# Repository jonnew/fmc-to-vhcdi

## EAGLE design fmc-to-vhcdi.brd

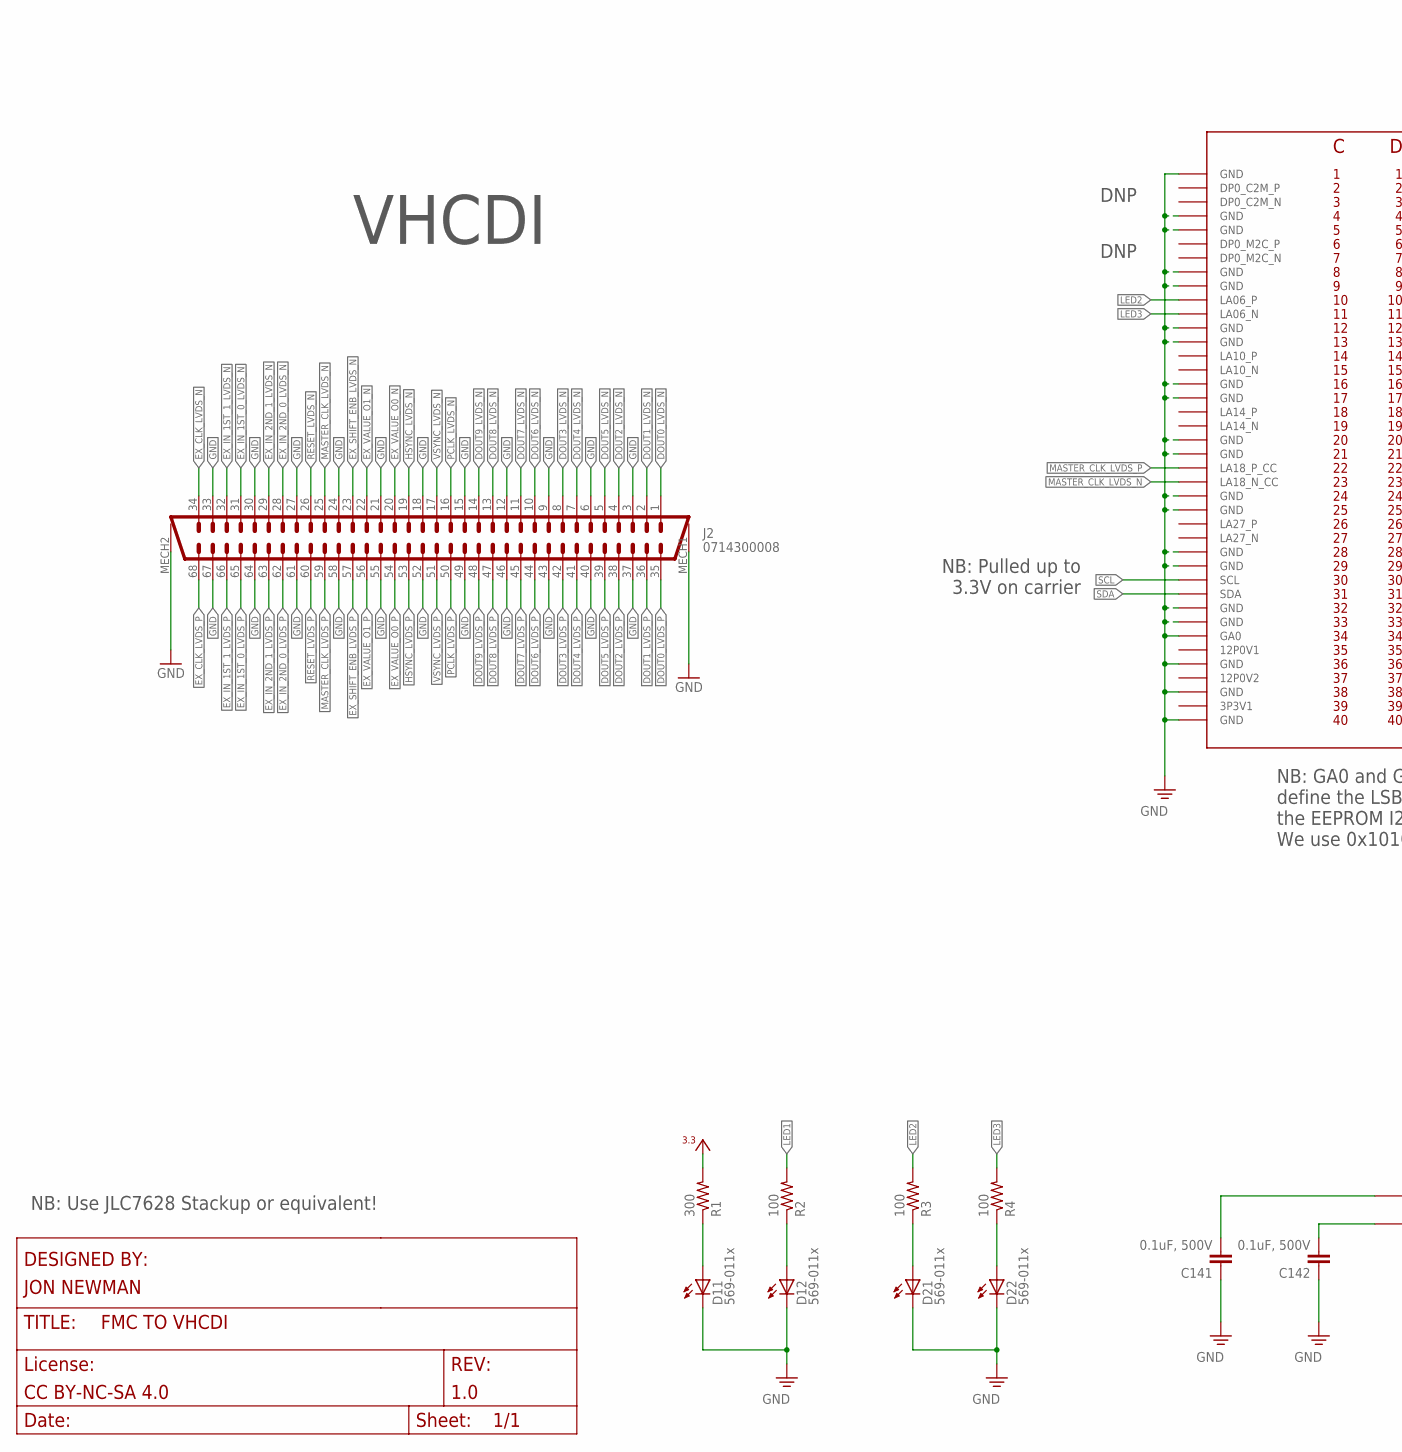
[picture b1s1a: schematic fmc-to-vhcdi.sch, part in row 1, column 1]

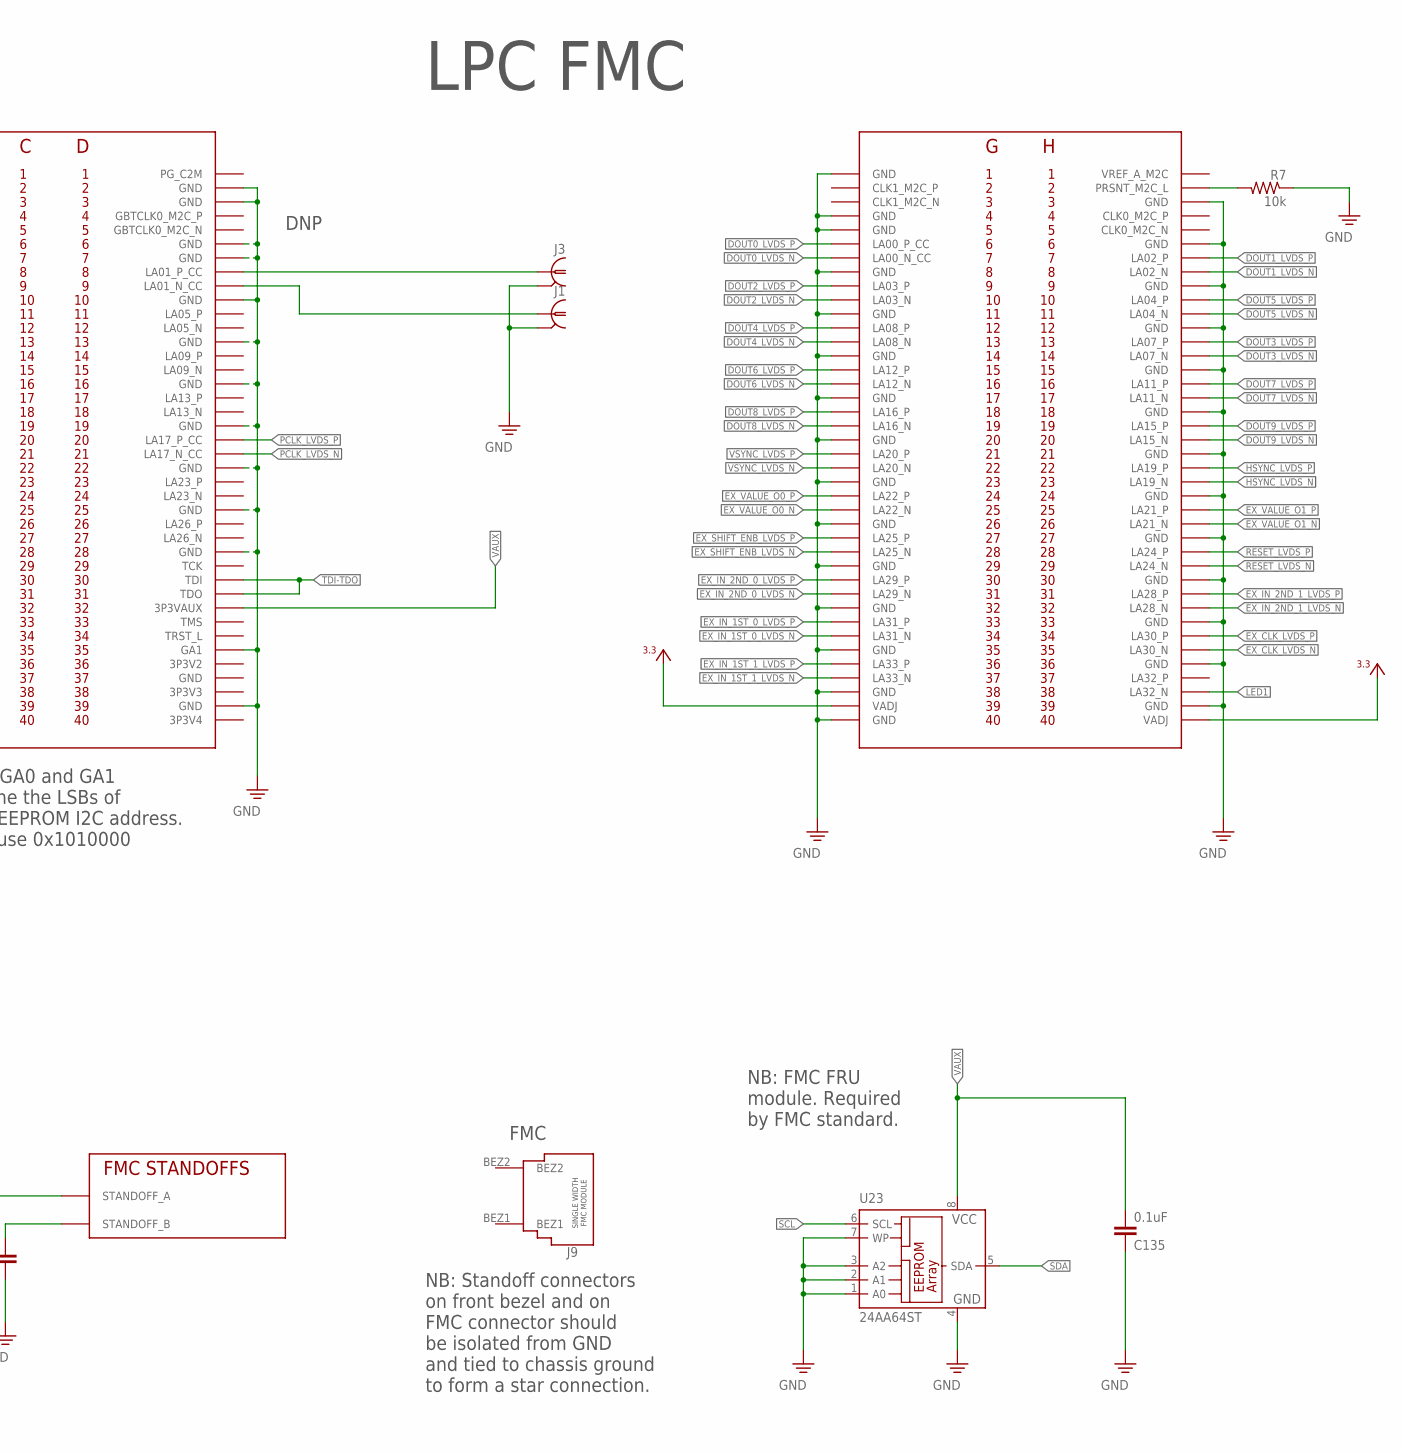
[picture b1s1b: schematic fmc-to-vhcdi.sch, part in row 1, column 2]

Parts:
C135: 0.1uF; 0402
C141, C142: 0.1uF, 500V; 1210
D1, D2: 569-011x; WP4060VH/2GD_LED_ARRAY
J1, J3: COAX_SMA-VERT; SMA_JACK_142-0701-201
J2: 0714300008; 0714300008-TIGHT
J4: FMC_LPC_160_PIN_MALE; FMC_LPC_MALE
J9: FMC_SINGLE_WIDTH_MODULE
R1: 300; 0402
R2, R3, R4: 100; 0402
R7: 10k; 0402
U23: 24AA64ST; TSSOP8

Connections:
+3V3: J4.G39 (VADJ), J4.H40 (VADJ), R1.2
DOUT0_LVDS_N: J2.1, J4.G7 (LA00_N_CC)
DOUT0_LVDS_P: J2.35, J4.G6 (LA00_P_CC)
DOUT1_LVDS_N: J2.2, J4.H8 (LA02_N)
DOUT1_LVDS_P: J2.36, J4.H7 (LA02_P)
DOUT2_LVDS_N: J2.4, J4.G10 (LA03_N)
DOUT2_LVDS_P: J2.38, J4.G9 (LA03_P)
DOUT3_LVDS_N: J2.8, J4.H14 (LA07_N)
DOUT3_LVDS_P: J2.42, J4.H13 (LA07_P)
DOUT4_LVDS_N: J2.7, J4.G13 (LA08_N)
DOUT4_LVDS_P: J2.41, J4.G12 (LA08_P)
DOUT5_LVDS_N: J2.5, J4.H11 (LA04_N)
DOUT5_LVDS_P: J2.39, J4.H10 (LA04_P)
DOUT6_LVDS_N: J2.10, J4.G16 (LA12_N)
DOUT6_LVDS_P: J2.44, J4.G15 (LA12_P)
DOUT7_LVDS_N: J2.11, J4.H17 (LA11_N)
DOUT7_LVDS_P: J2.45, J4.H16 (LA11_P)
DOUT8_LVDS_N: J2.13, J4.G19 (LA16_N)
DOUT8_LVDS_P: J2.47, J4.G18 (LA16_P)
DOUT9_LVDS_N: J2.14, J4.H20 (LA15_N)
DOUT9_LVDS_P: J2.48, J4.H19 (LA15_P)
EX_CLK_LVDS_N: J2.34, J4.H35 (LA30_N)
EX_CLK_LVDS_P: J2.68, J4.H34 (LA30_P)
EX_IN_1ST_0_LVDS_N: J2.31, J4.G34 (LA31_N)
EX_IN_1ST_0_LVDS_P: J2.65, J4.G33 (LA31_P)
EX_IN_1ST_1_LVDS_N: J2.32, J4.G37 (LA33_N)
EX_IN_1ST_1_LVDS_P: J2.66, J4.G36 (LA33_P)
EX_IN_2ND_0_LVDS_N: J2.28, J4.G31 (LA29_N)
EX_IN_2ND_0_LVDS_P: J2.62, J4.G30 (LA29_P)
EX_IN_2ND_1_LVDS_N: J2.29, J4.H32 (LA28_N)
EX_IN_2ND_1_LVDS_P: J2.63, J4.H31 (LA28_P)
EX_SHIFT_ENB_LVDS_N: J2.23, J4.G28 (LA25_N)
EX_SHIFT_ENB_LVDS_P: J2.57, J4.G27 (LA25_P)
EX_VALUE_O0_N: J2.20, J4.G25 (LA22_N)
EX_VALUE_O0_P: J2.54, J4.G24 (LA22_P)
EX_VALUE_O1_N: J2.22, J4.H26 (LA21_N)
EX_VALUE_O1_P: J2.56, J4.H25 (LA21_P)
GND: C135.1, C141.1, C142.1, D1.C1 (C), D1.C2 (C), D2.C1 (C), D2.C2 (C), J1.GND$1 (2), J1.GND$2 (2), J1.GND$3 (2), J1.GND$4 (2), J2.3, J2.6, J2.9, J2.12, J2.15, J2.18, J2.21, J2.24, J2.27, J2.30, J2.33, J2.37, J2.40, J2.43, J2.46, J2.49, J2.52, J2.55, J2.58, J2.61, J2.64, J2.67, J2.MECH1, J2.MECH2, J3.GND$1 (2), J3.GND$2 (2), J3.GND$3 (2), J3.GND$4 (2), J4.C1 (GND), J4.C4 (GND), J4.C5 (GND), J4.C8 (GND), J4.C9 (GND), J4.C12 (GND), J4.C13 (GND), J4.C16 (GND), J4.C17 (GND), J4.C20 (GND), J4.C21 (GND), J4.C24 (GND), J4.C25 (GND), J4.C28 (GND), J4.C29 (GND), J4.C32 (GND), J4.C33 (GND), J4.C34 (GA0), J4.C36 (GND), J4.C38 (GND), J4.C40 (GND), J4.D2 (GND), J4.D3 (GND), J4.D6 (GND), J4.D7 (GND), J4.D10 (GND), J4.D13 (GND), J4.D16 (GND), J4.D19 (GND), J4.D22 (GND), J4.D25 (GND), J4.D28 (GND), J4.D35 (GA1), J4.D37 (GND), J4.D39 (GND), J4.G1 (GND), J4.G4 (GND), J4.G5 (GND), J4.G8 (GND), J4.G11 (GND), J4.G14 (GND), J4.G17 (GND), J4.G20 (GND), J4.G23 (GND), J4.G26 (GND), J4.G29 (GND), J4.G32 (GND), J4.G35 (GND), J4.G38 (GND), J4.G40 (GND), J4.H3 (GND), J4.H6 (GND), J4.H9 (GND), J4.H12 (GND), J4.H15 (GND), J4.H18 (GND), J4.H21 (GND), J4.H24 (GND), J4.H27 (GND), J4.H30 (GND), J4.H33 (GND), J4.H36 (GND), J4.H39 (GND), R7.1, U23.1 (A0), U23.2 (A1), U23.3 (A2), U23.4 (GND), U23.7 (WP)
HSYNC_LVDS_N: J2.19, J4.H23 (LA19_N)
HSYNC_LVDS_P: J2.53, J4.H22 (LA19_P)
LED1: J4.H38 (LA32_N), R2.2
LED2: J4.C10 (LA06_P), R3.2
LED3: J4.C11 (LA06_N), R4.2
MASTER_CLK_LVDS_N: J2.25, J4.C23 (LA18_N_CC)
MASTER_CLK_LVDS_P: J2.59, J4.C22 (LA18_P_CC)
unnamed: D1.A2 (A), R2.1
unnamed: D2.A1 (A), R3.1
unnamed: D2.A2 (A), R4.1
unnamed: J4.H2 (PRSNT_M2C_L), R7.2
unnamed: D1.A1 (A), R1.1
unnamed: C142.2, J4.CHASSIS_B (STANDOFF_B)
unnamed: C141.2, J4.CHASSIS_A (STANDOFF_A)
PCLK_LVDS_N: J2.16, J4.D21 (LA17_N_CC)
PCLK_LVDS_P: J2.50, J4.D20 (LA17_P_CC)
RESET_LVDS_N: J2.26, J4.H29 (LA24_N)
RESET_LVDS_P: J2.60, J4.H28 (LA24_P)
SCL: J4.C30 (SCL), U23.6 (SCL)
SDA: J4.C31 (SDA), U23.5 (SDA)
SMA_N: J1.CLK (1), J4.D9 (LA01_N_CC)
SMA_P: J3.CLK (1), J4.D8 (LA01_P_CC)
TDI-TDO: J4.D30 (TDI), J4.D31 (TDO)
VAUX: C135.2, J4.D32 (3P3VAUX), U23.8 (VCC)
VSYNC_LVDS_N: J2.17, J4.G22 (LA20_N)
VSYNC_LVDS_P: J2.51, J4.G21 (LA20_P)

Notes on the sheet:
FMC
DNP
NB: GA0 and GA1 define the LSBs of the EEPROM I2C address. We use 0x1010000
NB: FMC FRU module. Required by FMC standard.
LPC FMC
NB: Standoff connectors on front bezel and on FMC connector should be isolated from GND and tied to chassis ground to form a star connection.
NB: Pulled up to 3.3V on carrier
NB: Use JLC7628 Stackup or equivalent!
VHCDI

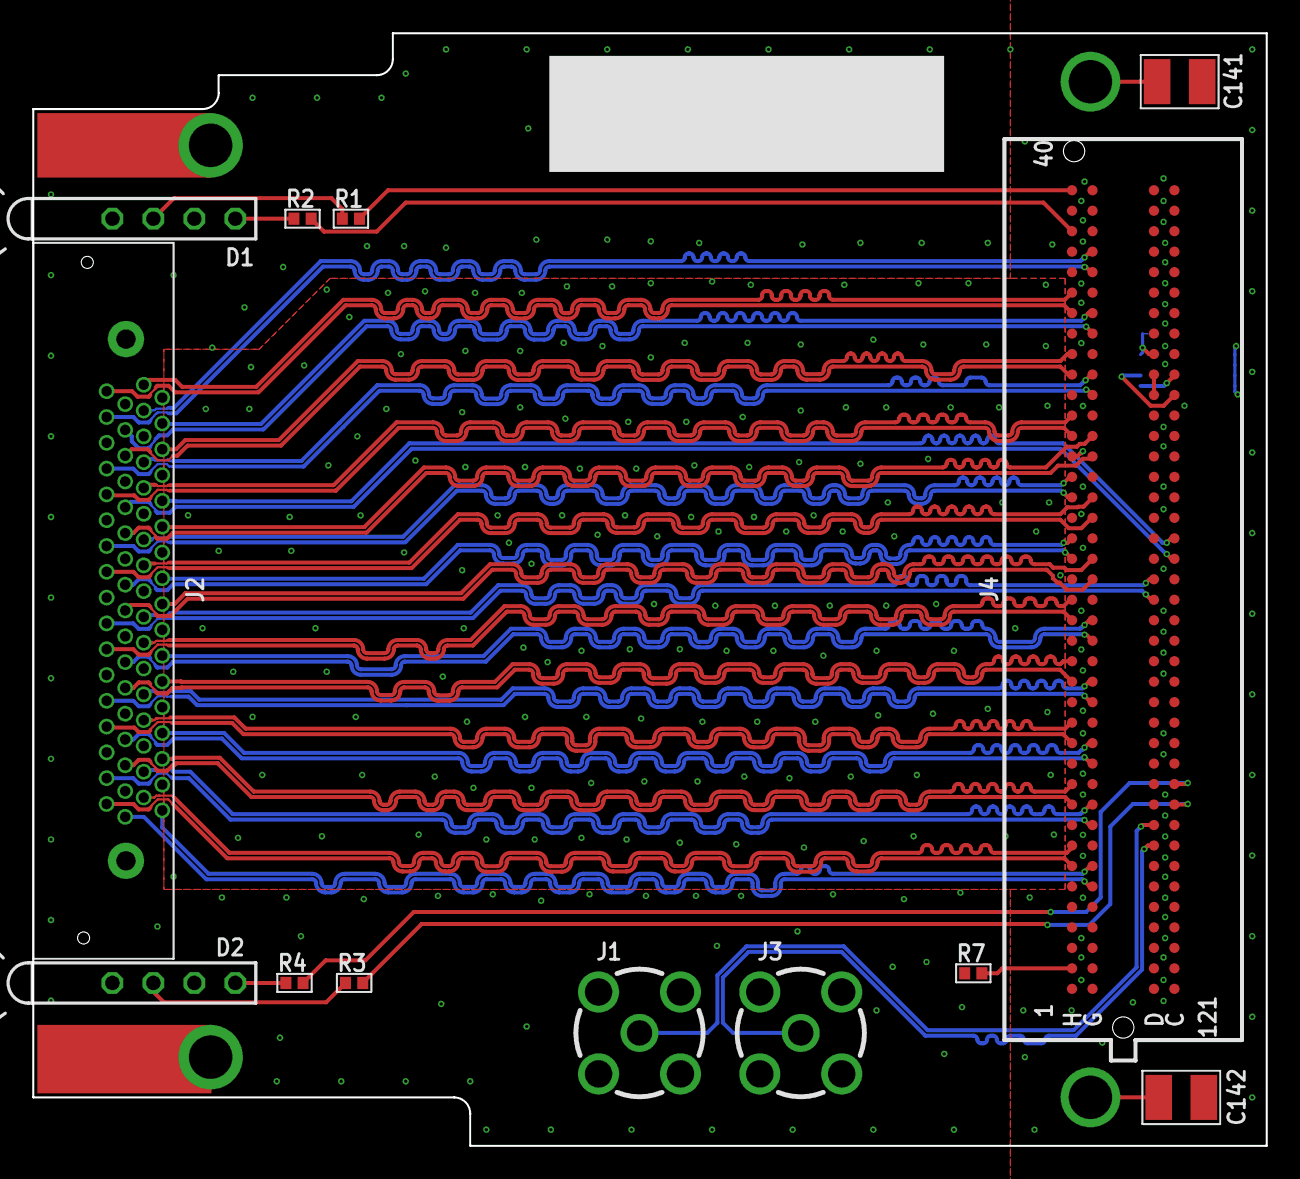
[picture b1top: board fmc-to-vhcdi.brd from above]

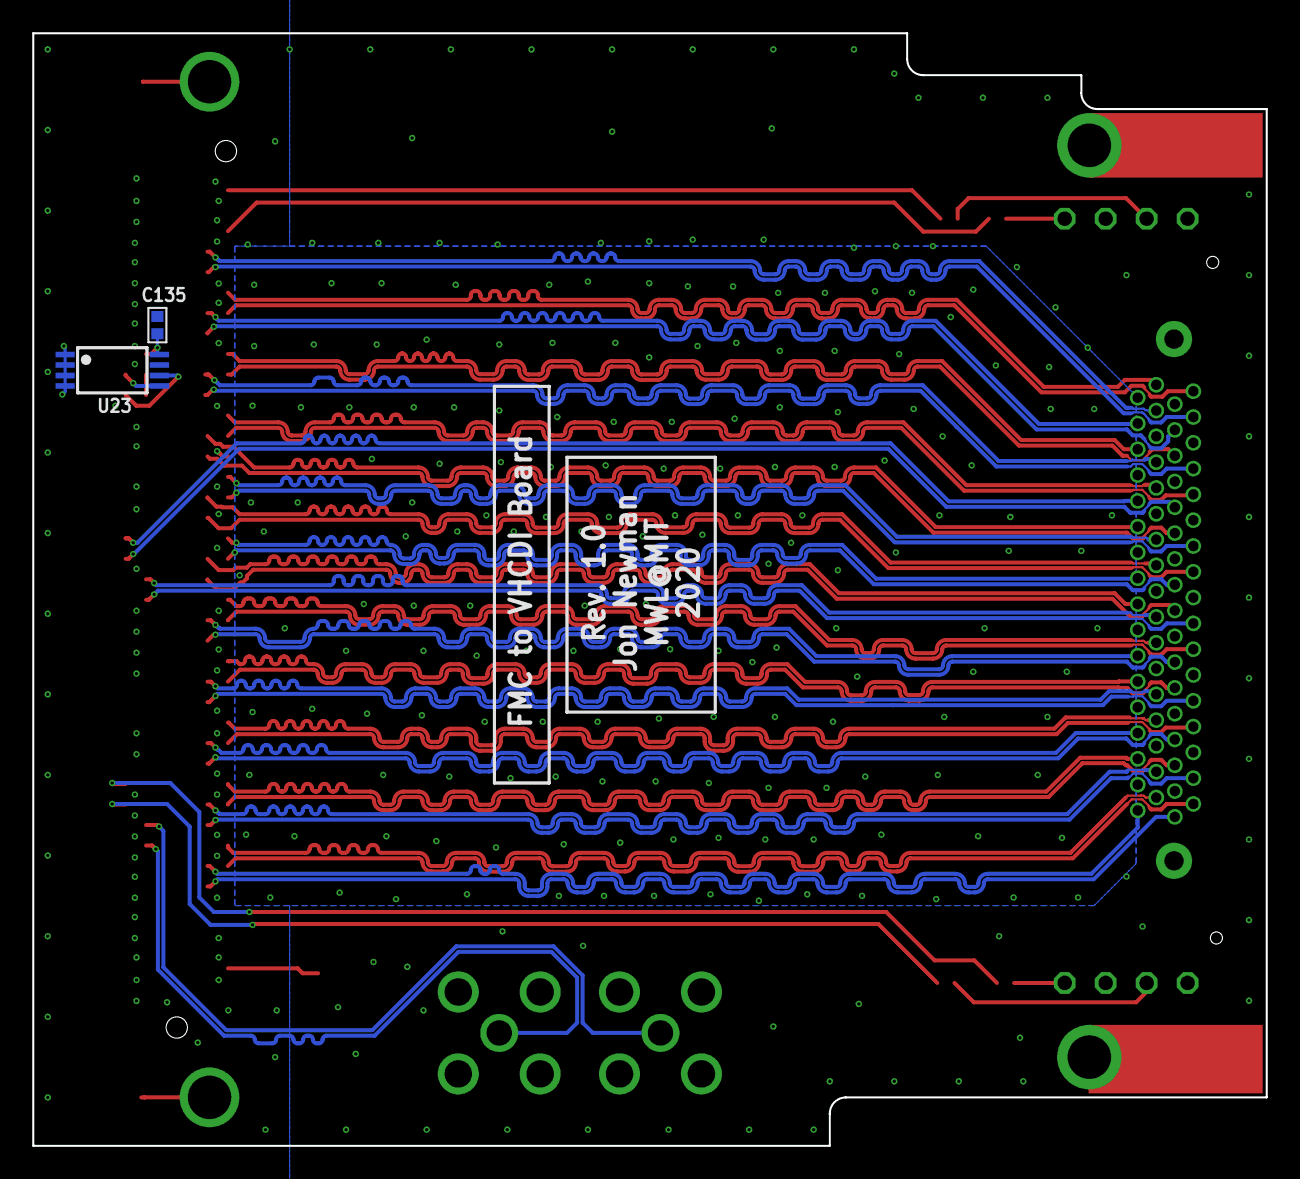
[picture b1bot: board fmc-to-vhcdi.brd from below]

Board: 4 copper layers, 76.5 x 69.0 mm, 16 parts (2 on the bottom side), 64 nets.

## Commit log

2021-01-20 Simple LPC FMC to VHCDI adapter boards
    - For Jacks project but might be useful elsewhere
2021-01-25 Minor updates to improve trace length equalization

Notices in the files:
fmc-to-vhcdi.sch:
LICENSE: CC BY-NC-SA 4.0
